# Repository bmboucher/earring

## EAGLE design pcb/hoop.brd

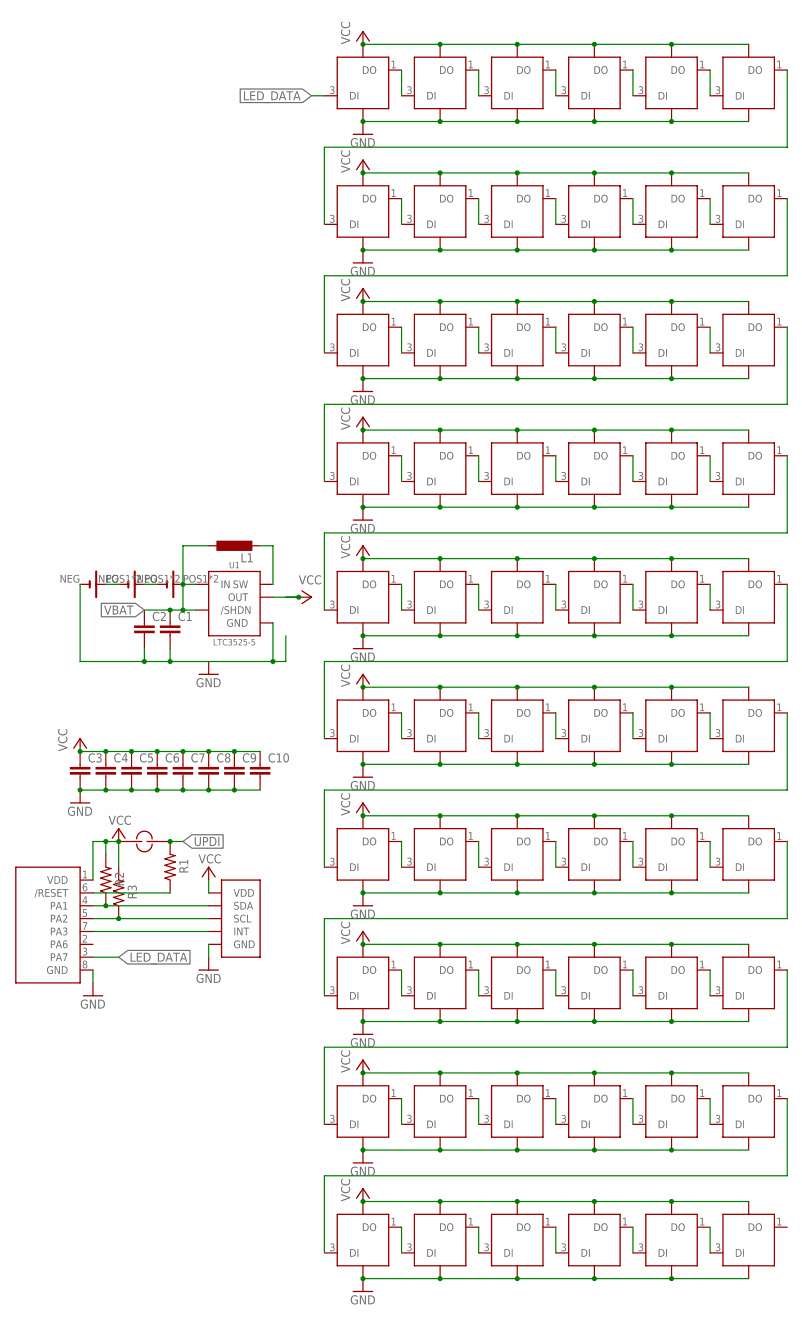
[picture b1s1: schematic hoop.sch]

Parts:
B1, B2, B3: P312; P312_CLIP
C1, C2, C3, C4, C5, C6, C7, C8, C9, C10: C-EUC0805; C0805
D1, D2, D3, D4, D5, D6, D7, D8, D9, D10, D11, D12, D13, D14, D15, D16, D17, D18, D19, D20, D21, D22, D23, D24, D25, D26, D27, D28, D29, D30, D31, D32, D33, D34, D35, D36, D37, D38, D39, D40, D41, D42, D43, D44, D45, D46, D47, D48, D49, D50, D51, D52, D53, D54, D55, D56, D57, D58, D59, D60: SMD-LX0707RGB-TR
J1: JMP; SOLDER_JMP
L1: L-EUL3216C; L3216C
R1, R2, R3: R-US_R0805; R0805
U1: LTC3525; SOP65P210X100-6N
U2: MXC6255XU; RESCAV110P300X300X105-6N
U3: ATTINY202; SOIC127P600X175-8N

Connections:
GND: B1.NEG (-), C1.2, C2.2, C3.2, C4.2, C5.2, C6.2, C7.2, C8.2, C9.2, C10.2, D1.4 (GND), D2.4 (GND), D3.4 (GND), D4.4 (GND), D5.4 (GND), D6.4 (GND), D7.4 (GND), D8.4 (GND), D9.4 (GND), D10.4 (GND), D11.4 (GND), D12.4 (GND), D13.4 (GND), D14.4 (GND), D15.4 (GND), D16.4 (GND), D17.4 (GND), D18.4 (GND), D19.4 (GND), D20.4 (GND), D21.4 (GND), D22.4 (GND), D23.4 (GND), D24.4 (GND), D25.4 (GND), D26.4 (GND), D27.4 (GND), D28.4 (GND), D29.4 (GND), D30.4 (GND), D31.4 (GND), D32.4 (GND), D33.4 (GND), D34.4 (GND), D35.4 (GND), D36.4 (GND), D37.4 (GND), D38.4 (GND), D39.4 (GND), D40.4 (GND), D41.4 (GND), D42.4 (GND), D43.4 (GND), D44.4 (GND), D45.4 (GND), D46.4 (GND), D47.4 (GND), D48.4 (GND), D49.4 (GND), D50.4 (GND), D51.4 (GND), D52.4 (GND), D53.4 (GND), D54.4 (GND), D55.4 (GND), D56.4 (GND), D57.4 (GND), D58.4 (GND), D59.4 (GND), D60.4 (GND), U1.2 (GND), U1.5 (GND), U2.6 (GND), U3.8 (GND)
LED_DATA: D1.3 (DI), U3.3 (PA7)
unnamed: D1.1 (DO), D2.3 (DI)
unnamed: D2.1 (DO), D3.3 (DI)
unnamed: D3.1 (DO), D4.3 (DI)
unnamed: D4.1 (DO), D5.3 (DI)
unnamed: D5.1 (DO), D6.3 (DI)
unnamed: D7.1 (DO), D8.3 (DI)
unnamed: D8.1 (DO), D9.3 (DI)
unnamed: D9.1 (DO), D10.3 (DI)
unnamed: D10.1 (DO), D11.3 (DI)
unnamed: D11.1 (DO), D12.3 (DI)
unnamed: D13.1 (DO), D14.3 (DI)
unnamed: D14.1 (DO), D15.3 (DI)
unnamed: D15.1 (DO), D16.3 (DI)
unnamed: D16.1 (DO), D17.3 (DI)
unnamed: D17.1 (DO), D18.3 (DI)
unnamed: D19.1 (DO), D20.3 (DI)
unnamed: D20.1 (DO), D21.3 (DI)
unnamed: D21.1 (DO), D22.3 (DI)
unnamed: D22.1 (DO), D23.3 (DI)
unnamed: D23.1 (DO), D24.3 (DI)
unnamed: D25.1 (DO), D26.3 (DI)
unnamed: D26.1 (DO), D27.3 (DI)
unnamed: D27.1 (DO), D28.3 (DI)
unnamed: D28.1 (DO), D29.3 (DI)
unnamed: B1.POS1 (+), B1.POS2 (+), B2.NEG (-)
unnamed: B2.POS1 (+), B2.POS2 (+), B3.NEG (-)
unnamed: D29.1 (DO), D30.3 (DI)
unnamed: D31.1 (DO), D32.3 (DI)
unnamed: D32.1 (DO), D33.3 (DI)
unnamed: D33.1 (DO), D34.3 (DI)
unnamed: D34.1 (DO), D35.3 (DI)
unnamed: D35.1 (DO), D36.3 (DI)
unnamed: D37.1 (DO), D38.3 (DI)
unnamed: D38.1 (DO), D39.3 (DI)
unnamed: D39.1 (DO), D40.3 (DI)
unnamed: D40.1 (DO), D41.3 (DI)
unnamed: D41.1 (DO), D42.3 (DI)
unnamed: D43.1 (DO), D44.3 (DI)
unnamed: D44.1 (DO), D45.3 (DI)
unnamed: D45.1 (DO), D46.3 (DI)
unnamed: D46.1 (DO), D47.3 (DI)
unnamed: D47.1 (DO), D48.3 (DI)
unnamed: D49.1 (DO), D50.3 (DI)
unnamed: D50.1 (DO), D51.3 (DI)
unnamed: D51.1 (DO), D52.3 (DI)
unnamed: D52.1 (DO), D53.3 (DI)
unnamed: D53.1 (DO), D54.3 (DI)
unnamed: D55.1 (DO), D56.3 (DI)
unnamed: D56.1 (DO), D57.3 (DI)
unnamed: D57.1 (DO), D58.3 (DI)
unnamed: D58.1 (DO), D59.3 (DI)
unnamed: D59.1 (DO), D60.3 (DI)
unnamed: D6.1 (DO), D7.3 (DI)
unnamed: D12.1 (DO), D13.3 (DI)
unnamed: D18.1 (DO), D19.3 (DI)
unnamed: D24.1 (DO), D25.3 (DI)
unnamed: D30.1 (DO), D31.3 (DI)
unnamed: D36.1 (DO), D37.3 (DI)
unnamed: D42.1 (DO), D43.3 (DI)
unnamed: D48.1 (DO), D49.3 (DI)
unnamed: D54.1 (DO), D55.3 (DI)
unnamed: L1.2, U1.6 (SW)
unnamed: U2.1 (INT), U3.7 (PA3)
unnamed: R1.1, U3.6 (/RESET)
SCL: R3.1, U2.4 (SCL), U3.5 (PA2)
SDA: R2.1, U2.5 (SDA), U3.4 (PA1)
UPDI: J1.P$2, R1.2
VBAT: B3.POS1 (+), B3.POS2 (+), C1.1, C2.1, L1.1, U1.1 (/SHDN), U1.3 (IN)
VCC: C3.1, C4.1, C5.1, C6.1, C7.1, C8.1, C9.1, C10.1, D1.2 (VDD), D2.2 (VDD), D3.2 (VDD), D4.2 (VDD), D5.2 (VDD), D6.2 (VDD), D7.2 (VDD), D8.2 (VDD), D9.2 (VDD), D10.2 (VDD), D11.2 (VDD), D12.2 (VDD), D13.2 (VDD), D14.2 (VDD), D15.2 (VDD), D16.2 (VDD), D17.2 (VDD), D18.2 (VDD), D19.2 (VDD), D20.2 (VDD), D21.2 (VDD), D22.2 (VDD), D23.2 (VDD), D24.2 (VDD), D25.2 (VDD), D26.2 (VDD), D27.2 (VDD), D28.2 (VDD), D29.2 (VDD), D30.2 (VDD), D31.2 (VDD), D32.2 (VDD), D33.2 (VDD), D34.2 (VDD), D35.2 (VDD), D36.2 (VDD), D37.2 (VDD), D38.2 (VDD), D39.2 (VDD), D40.2 (VDD), D41.2 (VDD), D42.2 (VDD), D43.2 (VDD), D44.2 (VDD), D45.2 (VDD), D46.2 (VDD), D47.2 (VDD), D48.2 (VDD), D49.2 (VDD), D50.2 (VDD), D51.2 (VDD), D52.2 (VDD), D53.2 (VDD), D54.2 (VDD), D55.2 (VDD), D56.2 (VDD), D57.2 (VDD), D58.2 (VDD), D59.2 (VDD), D60.2 (VDD), J1.P$1, R2.2, R3.2, U1.4 (OUT), U2.3 (VDD), U3.1 (VDD)

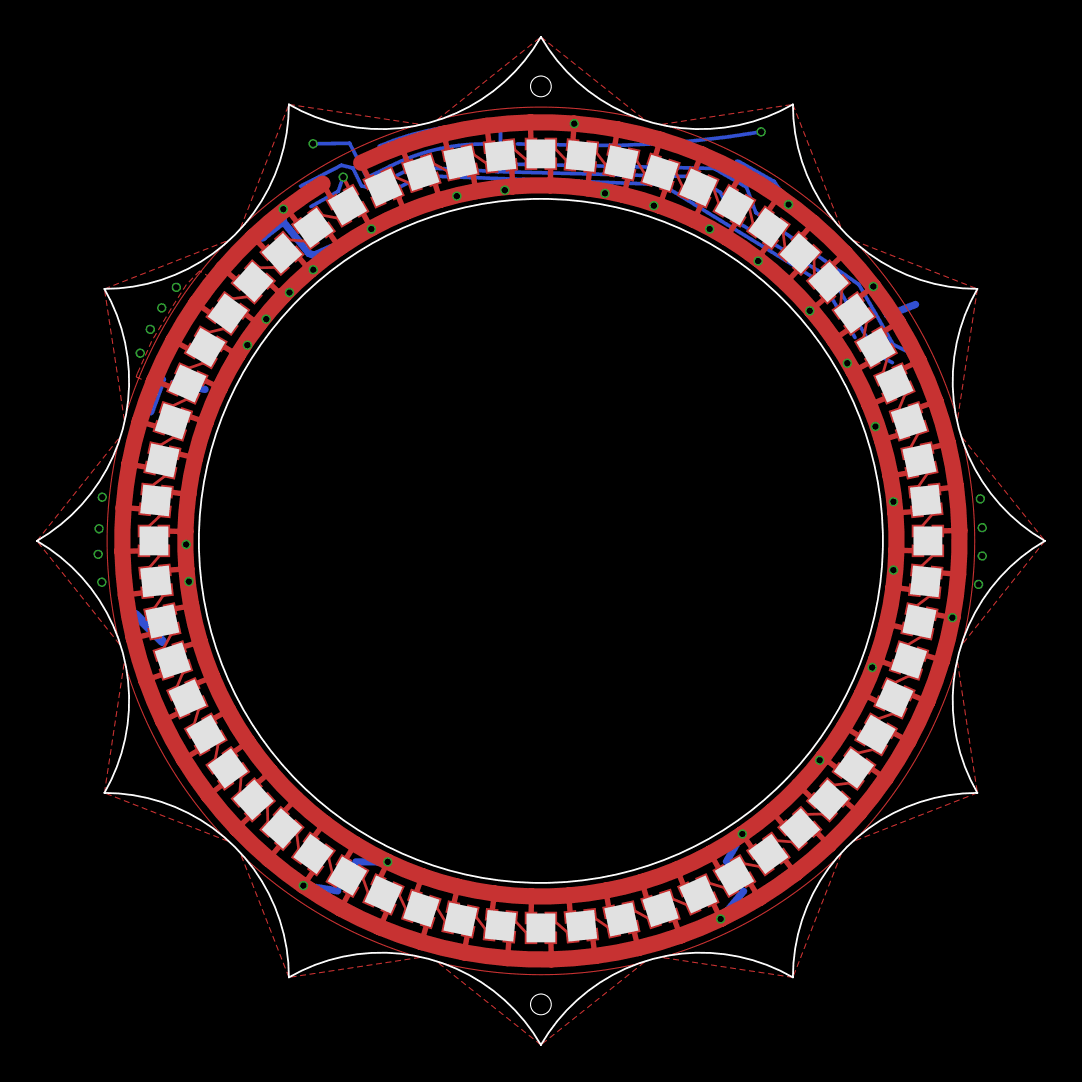
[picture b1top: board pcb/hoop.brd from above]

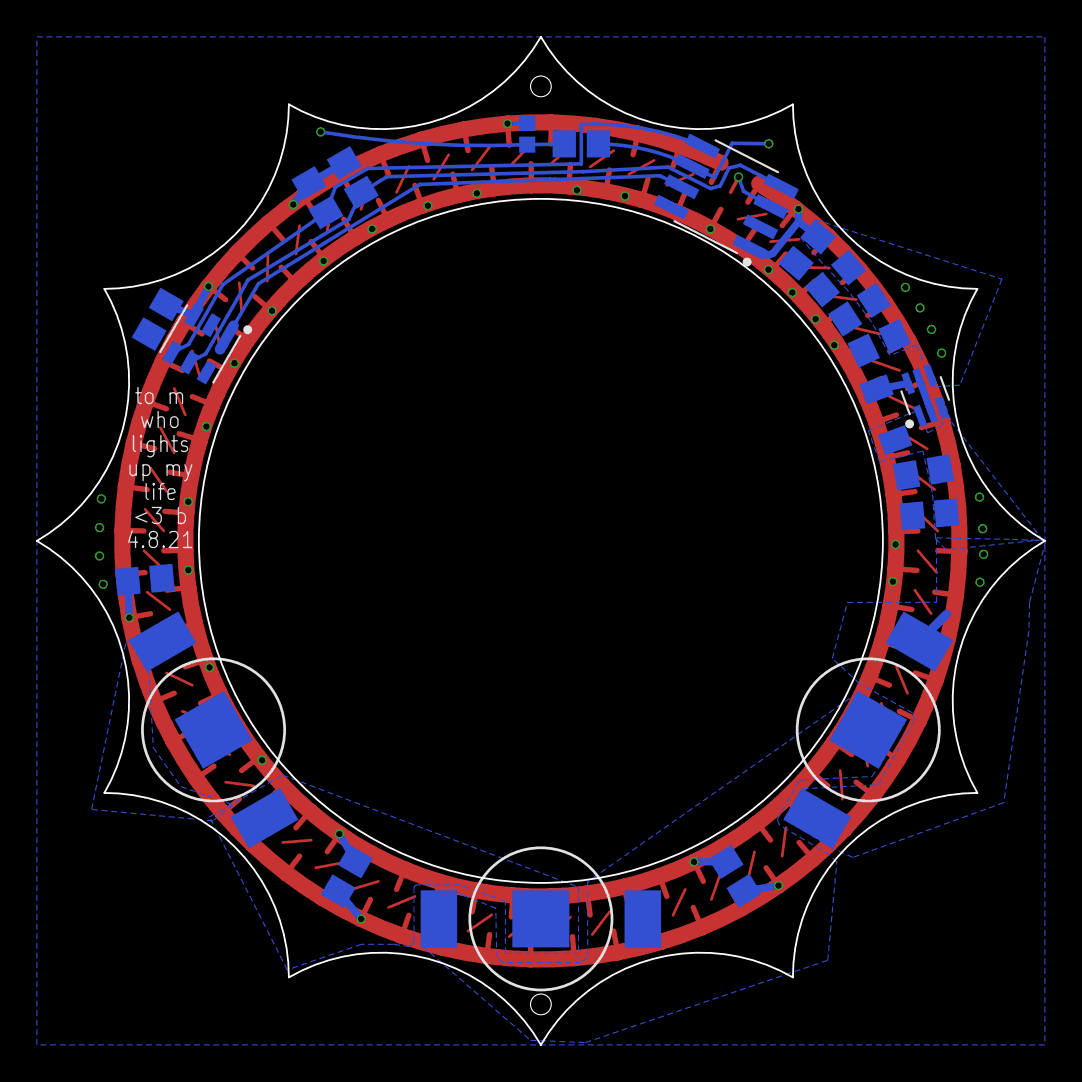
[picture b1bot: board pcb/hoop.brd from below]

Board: 2 copper layers, 56.0 x 56.0 mm, 81 parts (21 on the bottom side), 71 nets.

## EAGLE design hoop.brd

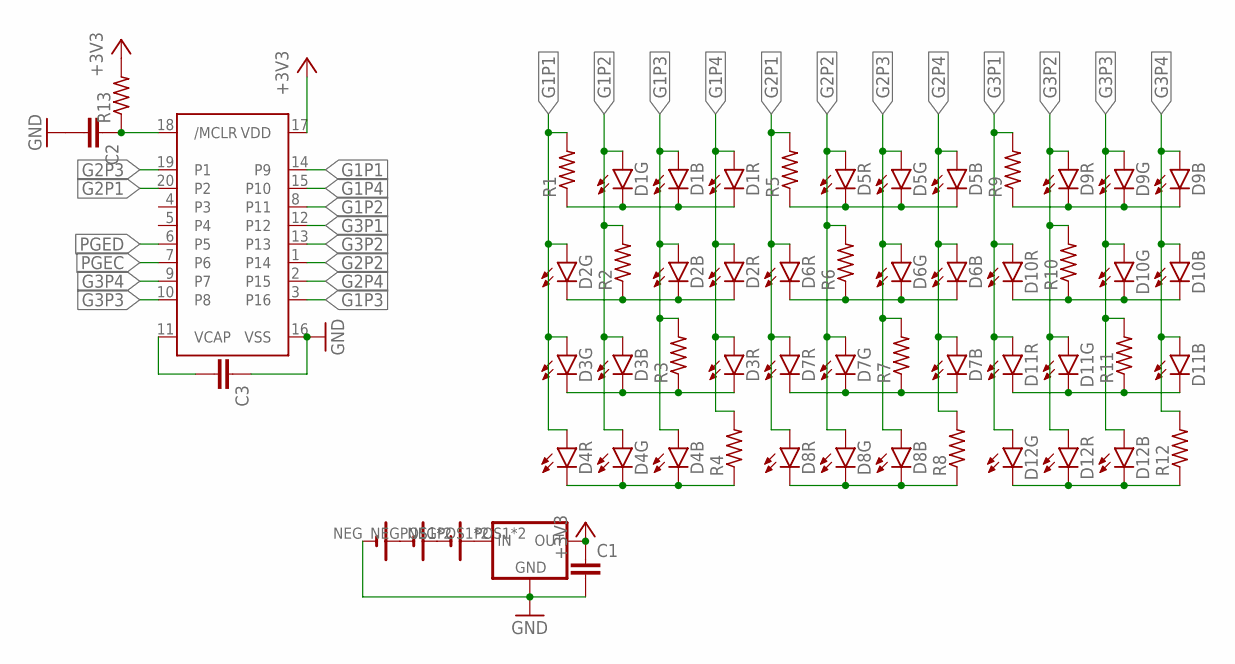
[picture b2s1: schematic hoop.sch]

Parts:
B1, B2, B3: P312; P312_CLIP
C1, C2, C3: C-EUC0402; C0402
D1, D2, D3, D4, D5, D6, D7, D8, D9, D10, D11, D12: FM-Z2727RGBA-SH; SMD_2.8X2.7MM
R1, R2, R3, R4, R5, R6, R7, R8, R9, R10, R11, R12: R-US_R0805; R0805
R13: R-US_R0402; R0402
U1: PIC32MM0064GPL020-I/ML; QFN50P400X400X100-21T280N
U2: SGM2200; SOT23

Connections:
+3V3: C1.1, R13.2, U1.17 (VDD), U2.2 (OUT)
/MCLR: C2.1, R13.1, U1.18 (/MCLR)
G1P1: D2.G+ (A), D3.G+ (A), D4.R+ (A), R1.2, U1.14 (P9)
G1P2: D1.G+ (A), D3.B+ (A), D4.G+ (A), R2.2, U1.8 (P11)
G1P3: D1.B+ (A), D2.B+ (A), D4.B+ (A), R3.2, U1.3 (P16)
G1P4: D1.R+ (A), D2.R+ (A), D3.R+ (A), R4.2, U1.15 (P10)
G2P1: D6.R+ (A), D7.R+ (A), D8.R+ (A), R5.2, U1.20 (P2)
G2P2: D5.R+ (A), D7.G+ (A), D8.G+ (A), R6.2, U1.1 (P14)
G2P3: D5.G+ (A), D6.G+ (A), D8.B+ (A), R7.2, U1.19 (P1)
G2P4: D5.B+ (A), D6.B+ (A), D7.B+ (A), R8.2, U1.2 (P15)
G3P1: D10.R+ (A), D11.R+ (A), D12.G+ (A), R9.2, U1.12
G3P2: D9.R+ (A), D11.G+ (A), D12.R+ (A), R10.2, U1.13
G3P3: D9.G+ (A), D10.G+ (A), D12.B+ (A), R11.2, U1.10 (P8)
G3P4: D9.B+ (A), D10.B+ (A), D11.B+ (A), R12.2, U1.9 (P7)
GND: B1.NEG (-), C1.2, C2.2, C3.1, U1.16 (VSS), U2.1 (GND)
unnamed: D1.B- (C), D1.G- (C), D1.R- (C), R1.1
unnamed: C3.2, U1.11 (VCAP)
unnamed: D2.B- (C), D2.G- (C), D2.R- (C), R2.1
unnamed: D4.B- (C), D4.G- (C), D4.R- (C), R4.1
unnamed: D3.B- (C), D3.G- (C), D3.R- (C), R3.1
unnamed: D12.B- (C), D12.G- (C), D12.R- (C), R12.1
unnamed: D5.B- (C), D5.G- (C), D5.R- (C), R5.1
unnamed: D6.B- (C), D6.G- (C), D6.R- (C), R6.1
unnamed: D7.B- (C), D7.G- (C), D7.R- (C), R7.1
unnamed: D8.B- (C), D8.G- (C), D8.R- (C), R8.1
unnamed: D9.B- (C), D9.G- (C), D9.R- (C), R9.1
unnamed: D10.B- (C), D10.G- (C), D10.R- (C), R10.1
unnamed: D11.B- (C), D11.G- (C), D11.R- (C), R11.1
unnamed: B1.POS1 (+), B1.POS2 (+), B2.NEG (-)
unnamed: B2.POS1 (+), B2.POS2 (+), B3.NEG (-)
unnamed: B3.POS1 (+), B3.POS2 (+), U2.3 (IN)
PGEC: U1.7 (P6)
PGED: U1.6 (P5)

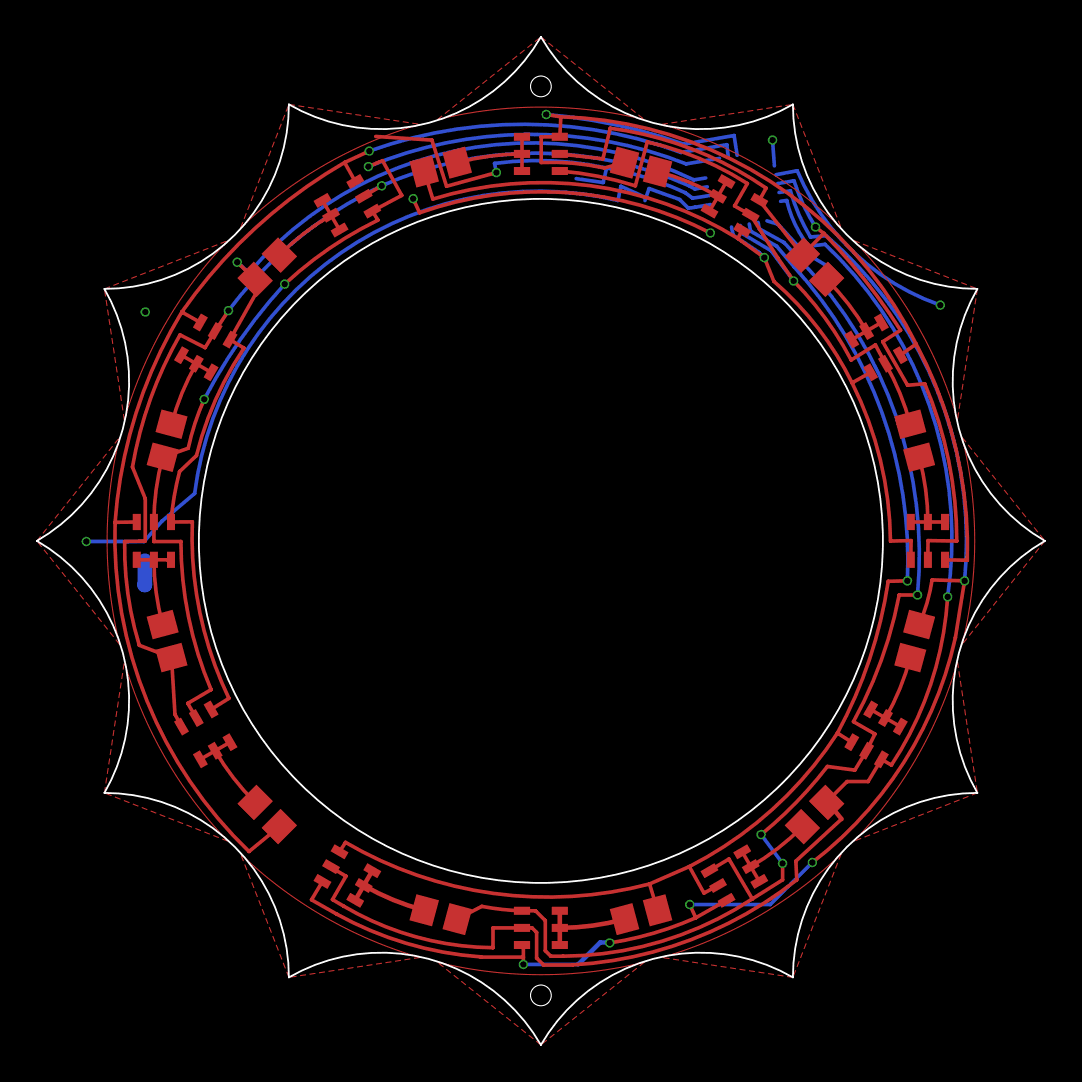
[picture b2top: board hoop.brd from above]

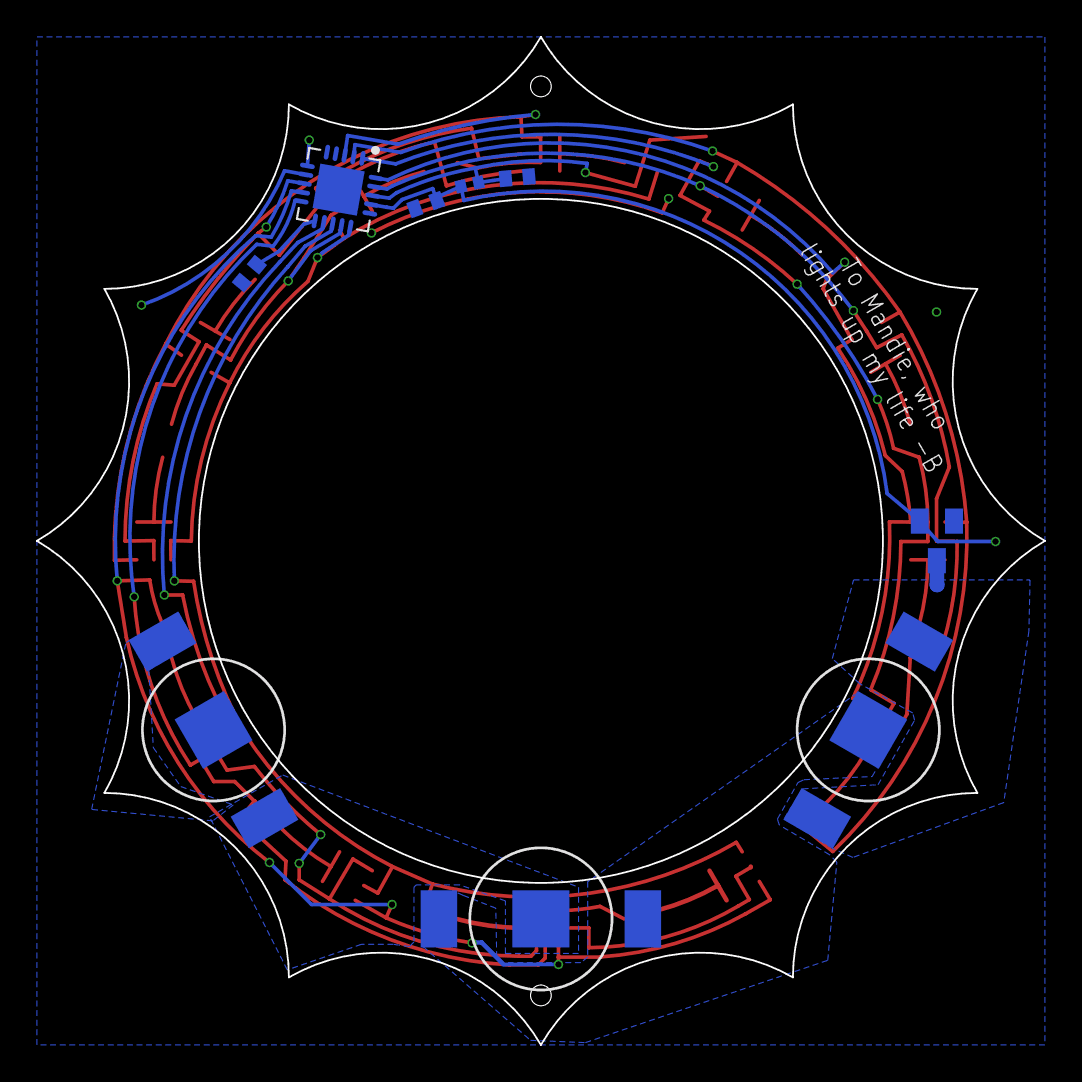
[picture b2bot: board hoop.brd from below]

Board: 2 copper layers, 56.0 x 56.0 mm, 33 parts (9 on the bottom side), 31 nets.

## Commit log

2021-03-12 First complete firmware
2021-03-12 Finalized firmware with comments
2021-03-12 Update board
2021-03-12 Cleaning up pcb files
2021-03-12 Creating "pcb" subfolder
